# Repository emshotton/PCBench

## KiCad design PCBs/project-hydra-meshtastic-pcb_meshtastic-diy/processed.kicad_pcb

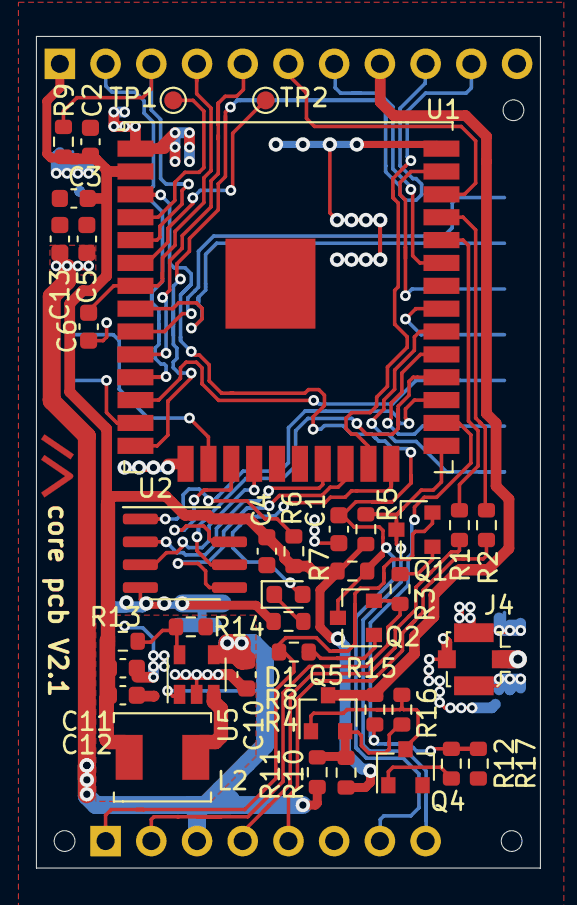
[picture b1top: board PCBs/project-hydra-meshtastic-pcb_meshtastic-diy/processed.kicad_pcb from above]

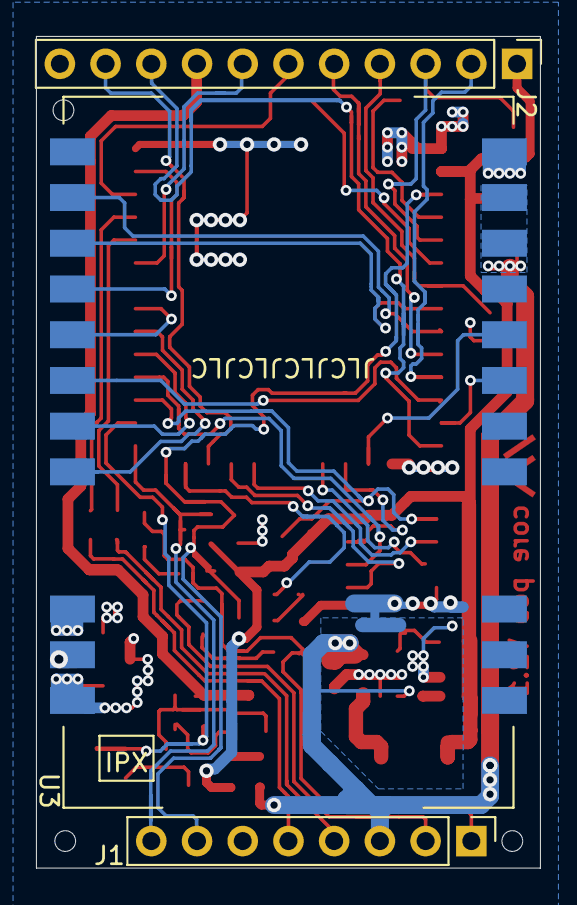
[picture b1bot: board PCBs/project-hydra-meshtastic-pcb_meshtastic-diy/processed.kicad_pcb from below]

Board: 2 copper layers, 28.0 x 46.2 mm, 47 parts (4 on the bottom side), 49 nets.

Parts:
C1, C2, C4, C5, C6: 100n; C_0603_1608Metric
C3, C10, C11, C12, C13: 22uF; C_0603_1608Metric
D1: LED; LED_0603_1608Metric
H1, H2, H3: tooling_hole; jlc_toolinghole
J1: programming header; PinHeader_1x08_P2.54mm_Vertical
J2: oled/gps/external HW; PinHeader_1x11_P2.54mm_Vertical
J4: ipex antenna; U.FL_Molex_MCRF_73412-0110_horizontal
L2: 4.7uH; chilsin_BMRA00040412
NT1: Net-Tie_2; NetTie-2_SMD_Pad0.5mm
Q1, Q2, Q4: BC848; SOT-23
Q5: CJ2301; SOT-23
R1, R8: 470; R_0603_1608Metric
R2, R10, R11, R16: 0; R_0603_1608Metric
R3, R4, R5, R6, R7, R9, R12, R15, R17: 10k; R_0603_1608Metric
R13: 536k; R_0603_1608Metric
R14: 118k; R_0603_1608Metric
SYM1: Meshtastic Logo; meshtastic_logo
TP1, TP2: TestPoint; TestPoint_Pad_D1.0mm
U1: ESP32-WROOM-32U
U2: ESP-PSRAM64; SOIC-8_3.9x4.9mm_P1.27mm
U3: E22-900M30S; e22-900m30s-handsoldering
U5: PAM2312; SOT-23-5

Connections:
+3V3: C2.1, C3.1, C4.1, C11.1, C12.1, J2.1, L2.2, R5.2, R6.2, R7.1, R9.2, R10.2, R13.1, U1.2, U2.8
+5V: C5.1, C10.1, C13.1, J1.3, R11.2, U3.9, U3.10, U5.1, U5.4
/5V_pwrctrl: J2.5, U1.10
/DTR: J1.1, Q1.2, R4.1
/EN: C1.1, J1.7, Q2.3, R7.2, U1.3
/ESP32_RX: R1.1, U1.34
/ESP32_TX: R2.1, U1.35
/GPIO0: J1.8, Q1.3, R5.1, U1.25
/GPIO2: D1.2, U1.24
/GPIO16: R6.1, U1.27, U2.1
/GPS_PWR_enable: R12.1, R16.2, R17.2, U1.26
/GPS_RX: J2.9, U1.14
/GPS_TX: J2.10, U1.23
/GPS_pwr: J2.8, Q5.3, R16.1
/RTS: J1.2, Q2.2, R3.1
/SCL: J2.6, U1.36
/SDA: J2.7, U1.33
/SDI_SD1: U1.22, U2.5
/SDO_SD0: U1.21, U2.2
/SHD_SD2: U1.17, U2.7
/SRAM_CLK: U1.28, U2.6
/SWP_SD3: U1.18, U2.3
/USR_BTN: J2.3, R9.1, U1.5
/e22_BUSY: U1.8, U3.14
/e22_DIO1: U1.9, U3.13
/e22_MISO: U1.31, U3.16
/e22_MOSI: U1.12, U3.17
/e22_NRST: U1.37, U3.15
/e22_NSS: U1.30, U3.19
/e22_RXEN: U1.13, U3.6
/e22_SCK: U1.29, U3.18
/e22_TXEN: U1.16, U3.7
/gpio_26: J2.2, U1.11
/vbat_mon: C6.1, J2.4, U1.7
GND: C1.2, C2.2, C3.2, C4.2, C5.2, C6.2, C13.2, J1.6, J2.11, J4.2, NT1.2, Q4.2, R8.2, R17.1, U1.1, U1.15, U1.38, U1.39, U2.4, U3.1, U3.2, U3.3, U3.4, U3.5, U3.11, U3.12, U3.20, U3.22
GNDA: C10.2, C11.2, C12.2, NT1.1, R14.2, U5.2
unnamed: D1.1, R8.1
unnamed: J1.4, R1.2
unnamed: J1.5, R2.2
unnamed: J4.1, U3.21
unnamed: L2.1, U5.3
unnamed: Q1.1, R3.2
unnamed: Q2.1, R4.2
unnamed: Q4.1, R12.2
unnamed: Q4.3, Q5.1, R15.1
unnamed: Q5.2, R10.1, R11.1, R15.2
unnamed: R13.2, R14.1, U5.5
unnamed: TP1.1, U1.4
unnamed: TP2.1, U1.6

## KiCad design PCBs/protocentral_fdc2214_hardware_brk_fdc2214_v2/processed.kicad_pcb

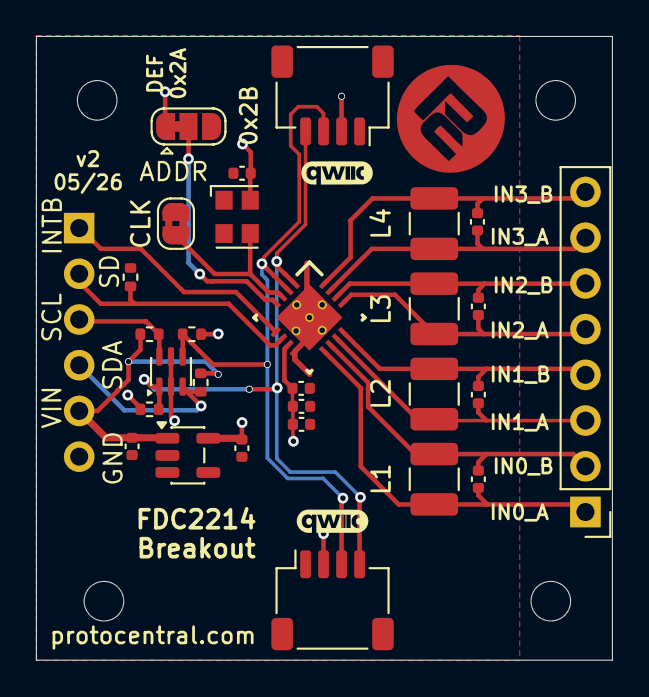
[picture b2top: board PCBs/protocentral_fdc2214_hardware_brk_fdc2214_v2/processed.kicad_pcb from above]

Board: 2 copper layers, 32.0 x 34.7 mm, 33 parts (0 on the bottom side), 19 nets.

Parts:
C1, C8: 1u; C_0402_1005Metric
C2: 2.2u; C_0402_1005Metric
C3, C9: 100n; C_0402_1005Metric
C4, C5, C6, C7: 33p; C_0402_1005Metric
C10: 10n; C_0402_1005Metric
CLK: SolderJumper_2_Bridged; SolderJumper-2_P1.3mm_Bridged2Bar_RoundedPad1.0x1.5mm
H1, H2, H3, H4: MountingHole; MountingHole_2.2mm_M2
J1: Conn_01x06; PinHeader_1x06_P2.54mm_Vertical
J2: Conn_01x08; PinHeader_1x08_P2.54mm_Vertical
J3, J4: Qwiic_RA; JST_SH_SM04B-SRSS-TB_1x04-1MP_P1.00mm_Horizontal
JP1: ADDR; SolderJumper-3_P1.3mm_Bridged12_RoundedPad1.0x1.5mm
L1, L2, L3, L4: 18uH, CMH322522-180KL; L_1210_3225Metric
R5, R8, R9, R12, R13: 10K; R_0402_1005Metric
U2: FDC2214RGHR; RGH0016A
U3: AP2112K-3.3; SOT-23-5
U4: BSS138DW-7-F; SOT-363_SC-70-6
Y1: KC2520Z; Oscillator_SMD_Kyocera_KC2520Z-4Pin_2.5x2.0mm

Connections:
+3V3: C2.1, C3.1, C8.1, C9.1, C10.1, J3.2, J4.2, JP1.1 (A), R8.1, R12.1, U2.7 (VDD), U3.5 (VOUT), U4.2 (G1), U4.5 (G2), Y1.4 (VCC)
GND: C1.2, C2.2, C3.2, C8.2, C9.2, C10.2, CLK.1 (A), J1.6, J3.1, J4.1, JP1.3 (B), R5.2, U2.8 (GND), U2.17, U3.2 (GND), Y1.2 (GND)
IN0_A: C4.1, J2.1, L1.2, U2.9 (IN0A)
IN0_B: C4.2, J2.2, L1.1, U2.10 (IN0B)
IN1_A: C5.1, J2.3, L2.2, U2.11 (IN1A)
IN1_B: C5.2, J2.4, L2.1, U2.12 (IN1B)
IN2_A: C6.1, J2.5, L3.2, U2.13 (IN2A)
IN2_B: C6.2, J2.6, L3.1, U2.14 (IN2B)
IN3_A: C7.1, J2.7, L4.2, U2.15 (IN3A)
IN3_B: C7.2, J2.8, L4.1, U2.16 (IN3B)
INTB: J1.1, U2.5 (INTB)
unnamed: JP1.2 (C), U2.4 (ADDR)
unnamed: CLK.2 (B), U2.3 (CLKIN), Y1.3 (CLK)
SCL: J1.3, R9.2, U4.6 (D1)
SCL_3V3: J3.4, J4.4, R8.2, U2.1 (SCL), U4.1 (S1)
SD: J1.2, R5.1, U2.6 (SD)
SDA: J1.4, R13.2, U4.3 (D2)
SDA_3V3: J3.3, J4.3, R12.2, U2.2 (SDA), U4.4 (S2)
VIN: C1.1, J1.5, R9.1, R13.1, U3.1 (VIN)

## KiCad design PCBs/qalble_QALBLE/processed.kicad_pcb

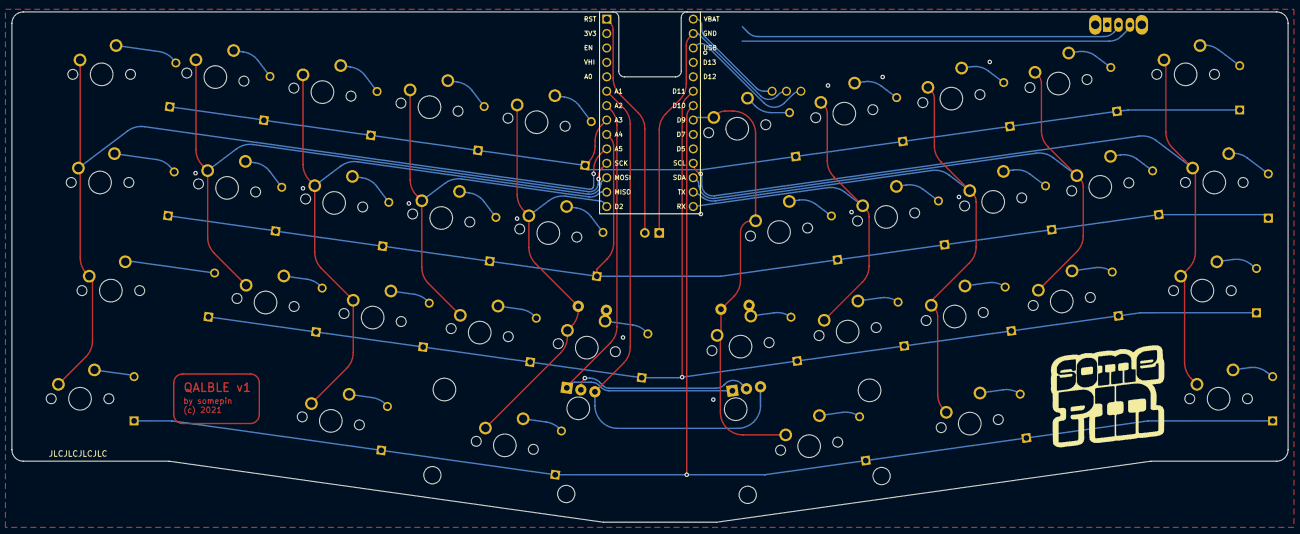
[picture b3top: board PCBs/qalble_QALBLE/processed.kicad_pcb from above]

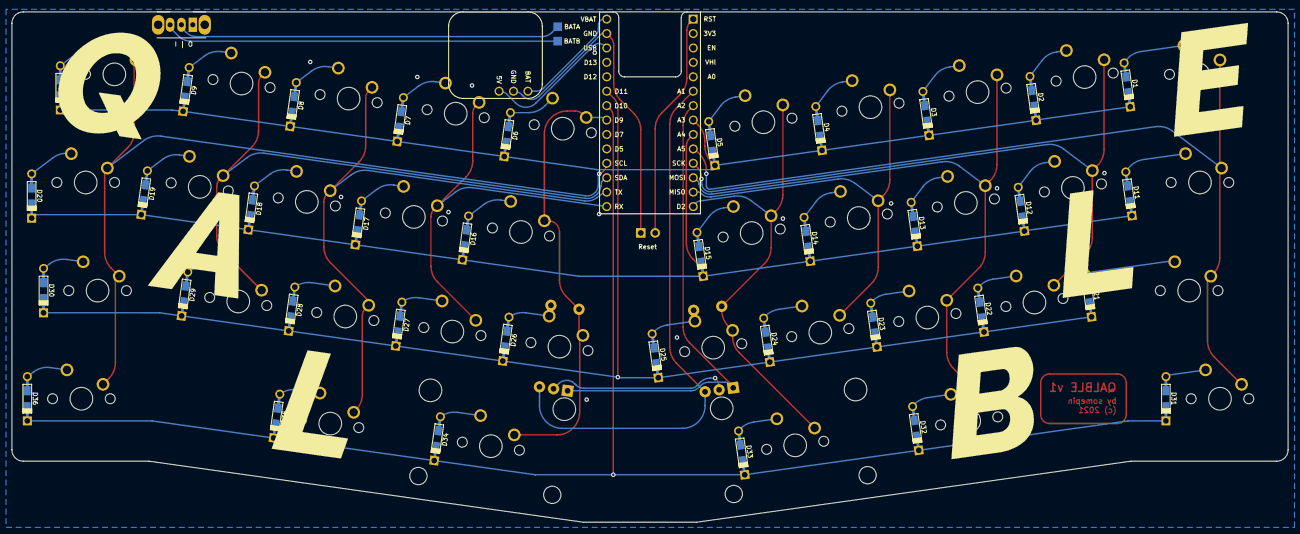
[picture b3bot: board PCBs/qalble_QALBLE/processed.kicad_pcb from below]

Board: 2 copper layers, 224.8 x 89.9 mm, 79 parts (3 on the bottom side), 58 nets.

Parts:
D1, D2, D3, D4, D5, D6, D7, D8, D9, D10, D11, D12, D13, D14, D15, D16, D17, D18, D19, D20, D21, D22, D23, D24, D25, D26, D27, D28, D29, D30, D31, D32, D33, D34, D35, D36: D_Small; Diode-Hybrid-Back
EN1, EN2: RotaryEncoder_Switch; RotaryEncoder_EC11
J1: Conn_01x02_Female; PinHeader_1x02_P2.54mm_Vertical
J2: Conn_01x02; Backpack Battery Jumper
MX1, MX2, MX3, MX4, MX5, MX6, MX7, MX8, MX9, MX12, MX13, MX14, MX15, MX16, MX17, MX18, MX19, MX20, MX22, MX23, MX24, MX25, MX26, MX27, MX28, MX29, MX31, MX32, MX35, MX36: MX-NoLED; MXOnly-1U-NoLED
MX10, MX11: MX-NoLED; MXOnly-1.25U-NoLED
MX21: MX-NoLED; MXOnly-1.75U-NoLED
MX30: MX-NoLED; MXOnly-1.5U-NoLED
MX33: MX-NoLED; MXOnly-2.25U-ReversedStabilizers-NoLED
MX34: MX-NoLED; MXOnly-2U-ReversedStabilizers-NoLED
SW1: SW_SPDT; SW_CuK_OS102011MA1QN1_SPDT_Angled
U1: Adafruit_ItsyBitsy_nRF52840; ItsyBitsy nRF52840
U2: Adafruit_Lipo_Backpack; Trinket Lipo Backpack

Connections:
BAT: U1.28 (VBAT), U2.3 (BAT)
BATA: J2.1, SW1.2 (B)
BATB: J2.2, SW1.3 (C)
COL0: MX1.1 (COL), MX11.1 (COL), MX21.1 (COL), MX31.1 (COL), U1.10 (A5)
COL1: MX2.1 (COL), MX12.1 (COL), MX22.1 (COL), U1.11 (SCK)
COL2: MX3.1 (COL), MX13.1 (COL), MX23.1 (COL), MX32.1 (COL), U1.12 (MOSI)
COL3: MX4.1 (COL), MX14.1 (COL), MX24.1 (COL), U1.13 (MISO)
COL4: EN1.S2, MX5.1 (COL), MX15.1 (COL), MX25.1 (COL), MX33.1 (COL), U1.14 (D2)
COL5: EN2.S2, MX6.1 (COL), MX16.1 (COL), MX26.1 (COL), MX34.1 (COL), U1.21 (D9)
COL6: MX7.1 (COL), MX17.1 (COL), MX27.1 (COL), U1.15 (RX)
COL7: MX8.1 (COL), MX18.1 (COL), MX28.1 (COL), MX35.1 (COL), U1.16 (TX)
COL8: MX9.1 (COL), MX19.1 (COL), MX29.1 (COL), U1.17 (SDA)
COL9: MX10.1 (COL), MX20.1 (COL), MX30.1 (COL), MX36.1 (COL), U1.18 (SCL)
ENCA: EN1.A, EN2.A, U1.7 (A2)
ENCB: EN1.B, EN2.B, U1.6 (A1)
GND: EN1.C, EN2.C, J1.1, U1.27 (GND), U2.2 (GND)
unnamed: D1.2 (A), MX1.2 (ROW)
unnamed: D2.2 (A), MX2.2 (ROW)
unnamed: D3.2 (A), MX3.2 (ROW)
unnamed: D4.2 (A), MX4.2 (ROW)
unnamed: D5.2 (A), MX5.2 (ROW)
unnamed: D6.2 (A), MX6.2 (ROW)
unnamed: D7.2 (A), MX7.2 (ROW)
unnamed: D8.2 (A), MX8.2 (ROW)
unnamed: D9.2 (A), MX9.2 (ROW)
unnamed: D10.2 (A), MX10.2 (ROW)
unnamed: D11.2 (A), MX11.2 (ROW)
unnamed: D12.2 (A), MX12.2 (ROW)
unnamed: D13.2 (A), MX13.2 (ROW)
unnamed: D14.2 (A), MX14.2 (ROW)
unnamed: D15.2 (A), MX15.2 (ROW)
unnamed: D16.2 (A), MX16.2 (ROW)
unnamed: D17.2 (A), MX17.2 (ROW)
unnamed: D18.2 (A), MX18.2 (ROW)
unnamed: D19.2 (A), MX19.2 (ROW)
unnamed: D20.2 (A), MX20.2 (ROW)
unnamed: D21.2 (A), MX21.2 (ROW)
unnamed: D22.2 (A), MX22.2 (ROW)
unnamed: D23.2 (A), MX23.2 (ROW)
unnamed: D24.2 (A), MX24.2 (ROW)
unnamed: D25.2 (A), EN1.S1, MX25.2 (ROW)
unnamed: D26.2 (A), EN2.S1, MX26.2 (ROW)
unnamed: D27.2 (A), MX27.2 (ROW)
unnamed: D28.2 (A), MX28.2 (ROW)
unnamed: D29.2 (A), MX29.2 (ROW)
unnamed: D30.2 (A), MX30.2 (ROW)
unnamed: D31.2 (A), MX31.2 (ROW)
unnamed: D32.2 (A), MX32.2 (ROW)
unnamed: D33.2 (A), MX33.2 (ROW)
unnamed: D34.2 (A), MX34.2 (ROW)
unnamed: D35.2 (A), MX35.2 (ROW)
unnamed: D36.2 (A), MX36.2 (ROW)
ROW0: D1.1 (K), D2.1 (K), D3.1 (K), D4.1 (K), D5.1 (K), D6.1 (K), D7.1 (K), D8.1 (K), D9.1 (K), D10.1 (K), U1.8 (A3)
ROW1: D11.1 (K), D12.1 (K), D13.1 (K), D14.1 (K), D15.1 (K), D16.1 (K), D17.1 (K), D18.1 (K), D19.1 (K), D20.1 (K), U1.9 (A4)
ROW2: D21.1 (K), D22.1 (K), D23.1 (K), D24.1 (K), D25.1 (K), D26.1 (K), D27.1 (K), D28.1 (K), D29.1 (K), D30.1 (K), U1.23 (D11)
ROW3: D31.1 (K), D32.1 (K), D33.1 (K), D34.1 (K), D35.1 (K), D36.1 (K), U1.22 (D10)
RST: J1.2, U1.1 (RST)
USB: U1.26 (USB), U2.1 (5V)

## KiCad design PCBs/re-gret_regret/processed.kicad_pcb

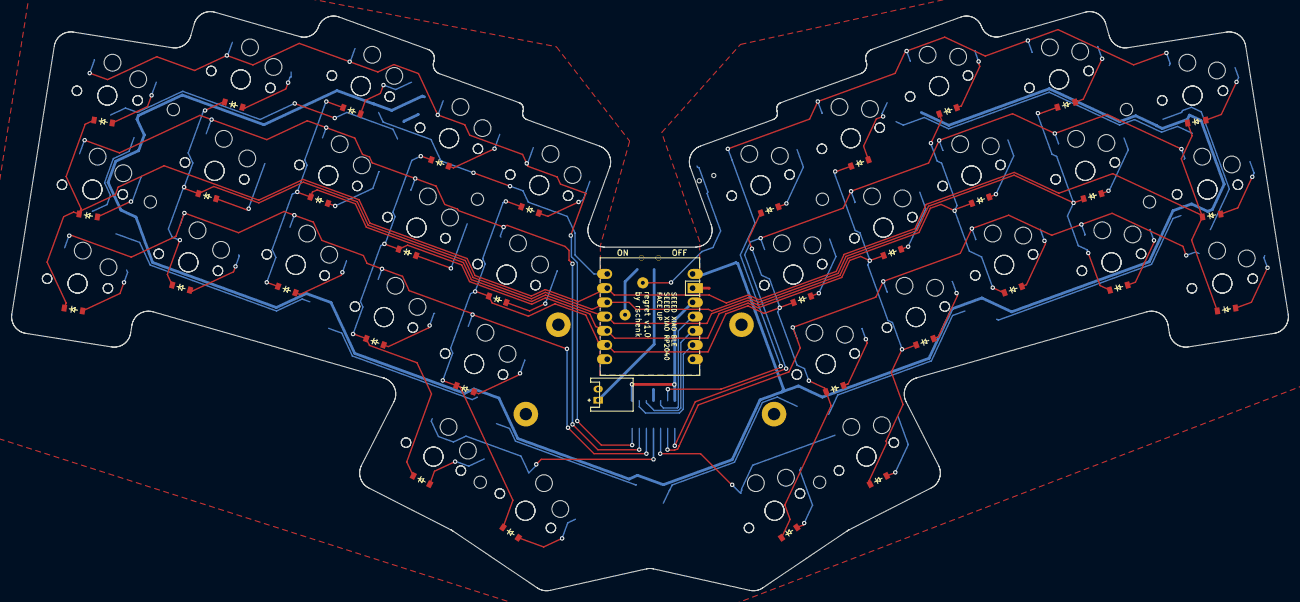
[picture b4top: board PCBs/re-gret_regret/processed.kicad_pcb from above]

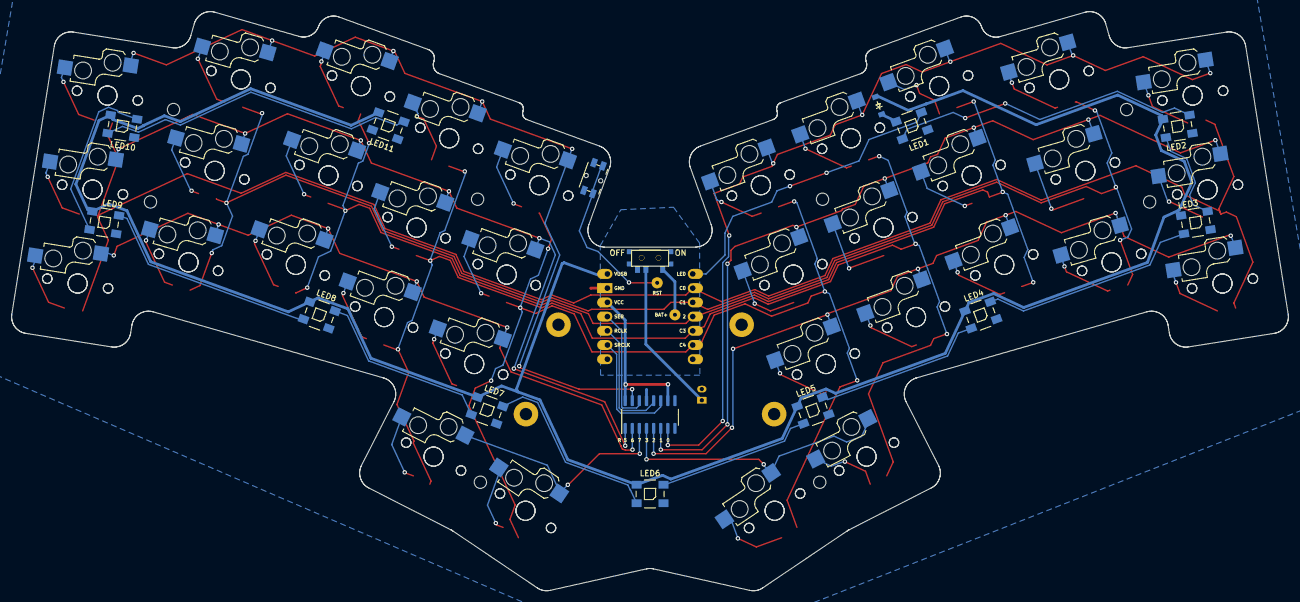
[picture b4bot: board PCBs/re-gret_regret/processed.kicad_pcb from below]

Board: 2 copper layers, 228.1 x 103.5 mm, 131 parts (13 on the bottom side), 68 nets.

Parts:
19.051: 74HC595; SOIC-16_3.9x9.9mm_P1.27mm
B1: Panasonic_EVQPUL_EVQPUC
D1, D2, D3, D4, D5, D6, D7, D8, D9, D10, D11, D12, D13, D14, D15, D16, D17, D18, D19, D20, D21, D22, D23, D24, D25, D26, D27, D28, D29, D30, D31, D32, D33, D34, D35: ComboDiode
JST1: JST_PH_S2B-PH-K_02x2.00mm_Angled
LED1, LED2, LED3, LED4, LED5, LED6, LED7, LED8, LED9, LED10, LED11: VAL**; WS2812B
MCU1: xiao-ble
PAD1, PAD2, PAD3, PAD4: MountingHole_2.2mm_M2_Pad
PAD5, PAD6, PAD7, PAD8, PAD9, PAD10, PAD11, PAD12: MountingHole_2.2mm_M2
S1, S2, S3, S4, S5, S6, S7, S8, S9, S10, S11, S12, S13, S14, S15, S16, S17, S18, S19, S20, S21, S22, S23, S24, S25, S26, S27, S28, S29, S30, S31, S32, S33, S34: PG1350
SB1, SB2, SB3, SB4, SB5, SB6, SB7, SB8, SB9, SB10, SB11, SB12, SB13, SB14, SB15, SB16, SB17, SB18, SB19, SB20, SB21, SB22, SB23, SB24, SB25, SB26, SB27, SB28, SB29, SB30, SB31, SB32, SB33, SB34: ChocBonusGoodies
T1: SPDT_C128955

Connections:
BAT+: MCU1.19, T1.1
BAT_POS: JST1.1, T1.2
C0: D1.1, D2.1, D3.1, D16.1, D17.1, D18.1, MCU1.2
C1: D4.1, D5.1, D6.1, D19.1, D20.1, D21.1, MCU1.3
C2: D7.1, D8.1, D9.1, D22.1, D23.1, D24.1, MCU1.4
C3: D10.1, D11.1, D12.1, D25.1, D26.1, D27.1, D31.1, D33.1, MCU1.5
C4: D13.1, D14.1, D15.1, D28.1, D29.1, D30.1, D32.1, D34.1, MCU1.6
GND: 19.051.8, 19.051.13, B1.2, JST1.2, LED1.3, LED2.3, LED3.3, LED4.3, LED5.3, LED6.3, LED7.3, LED8.3, LED9.3, LED10.3, LED11.3, MCU1.13
L2: LED1.2, LED2.4
L3: LED2.2, LED3.4
L4: LED3.2, LED4.4
L5: LED4.2, LED5.4
L6: LED5.2, LED6.4
L7: LED6.2, LED7.4
L8: LED7.2, LED8.4
L9: LED8.2, LED9.4
L10: LED9.2, LED10.4
L11: LED10.2, LED11.4
LED: LED1.4, MCU1.1
R0: 19.051.7, S3.1, S6.1, S9.1, S12.1, S15.1
R1: 19.051.6, S2.1, S5.1, S8.1, S11.1, S14.1
R2: 19.051.5, S1.1, S4.1, S7.1, S10.1, S13.1
R3: 19.051.4, S31.1, S32.1
R4: 19.051.15, S18.1, S21.1, S24.1, S27.1, S30.1
R5: 19.051.1, S17.1, S20.1, S23.1, S26.1, S29.1
R6: 19.051.2, S16.1, S19.1, S22.1, S25.1, S28.1
R7: 19.051.3, S33.1, S34.1
RCLK: 19.051.12, MCU1.10
RST: B1.1, MCU1.17
SER: 19.051.14, MCU1.11
SRCLK: 19.051.11, MCU1.9
VCC: 19.051.10, 19.051.16, MCU1.12
VUSB: D35.2, LED2.1, LED3.1, LED4.1, LED5.1, LED6.1, LED7.1, LED8.1, LED9.1, LED10.1, LED11.1, MCU1.14
home_thumb: D31.2, S31.2
index_bottom: D10.2, S10.2
index_home: D11.2, S11.2
index_top: D12.2, S12.2
inner_bottom: D13.2, S13.2
inner_home: D14.2, S14.2
inner_top: D15.2, S15.2
led_1_v: D35.1, LED1.1
middle_bottom: D7.2, S7.2
middle_home: D8.2, S8.2
middle_top: D9.2, S9.2
mirror_home_thumb: D33.2, S33.2
mirror_index_bottom: D25.2, S25.2
mirror_index_home: D26.2, S26.2
mirror_index_top: D27.2, S27.2
mirror_inner_bottom: D28.2, S28.2
mirror_inner_home: D29.2, S29.2
mirror_inner_top: D30.2, S30.2
mirror_middle_bottom: D22.2, S22.2
mirror_middle_home: D23.2, S23.2
mirror_middle_top: D24.2, S24.2
mirror_pinky_bottom: D16.2, S16.2
mirror_pinky_home: D17.2, S17.2
mirror_pinky_top: D18.2, S18.2
mirror_reachy_thumb: D34.2, S34.2
mirror_ring_bottom: D19.2, S19.2
mirror_ring_home: D20.2, S20.2
mirror_ring_top: D21.2, S21.2
pinky_bottom: D1.2, S1.2
pinky_home: D2.2, S2.2
pinky_top: D3.2, S3.2
reachy_thumb: D32.2, S32.2
ring_bottom: D4.2, S4.2
ring_home: D5.2, S5.2
ring_top: D6.2, S6.2

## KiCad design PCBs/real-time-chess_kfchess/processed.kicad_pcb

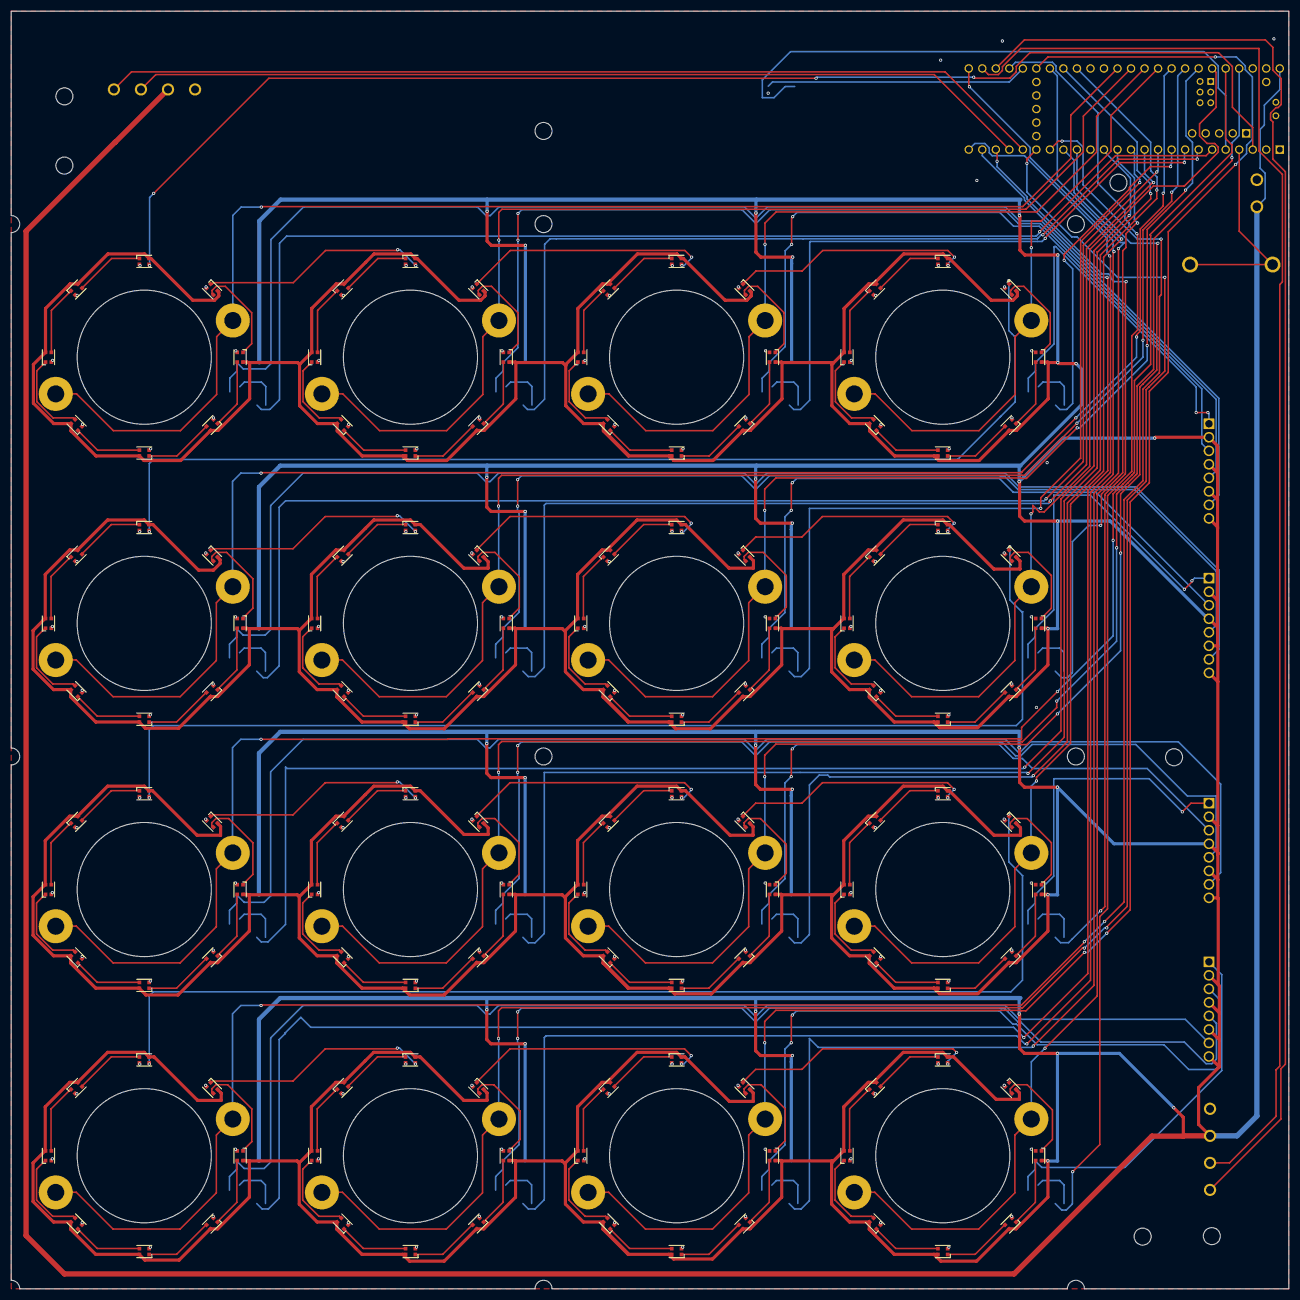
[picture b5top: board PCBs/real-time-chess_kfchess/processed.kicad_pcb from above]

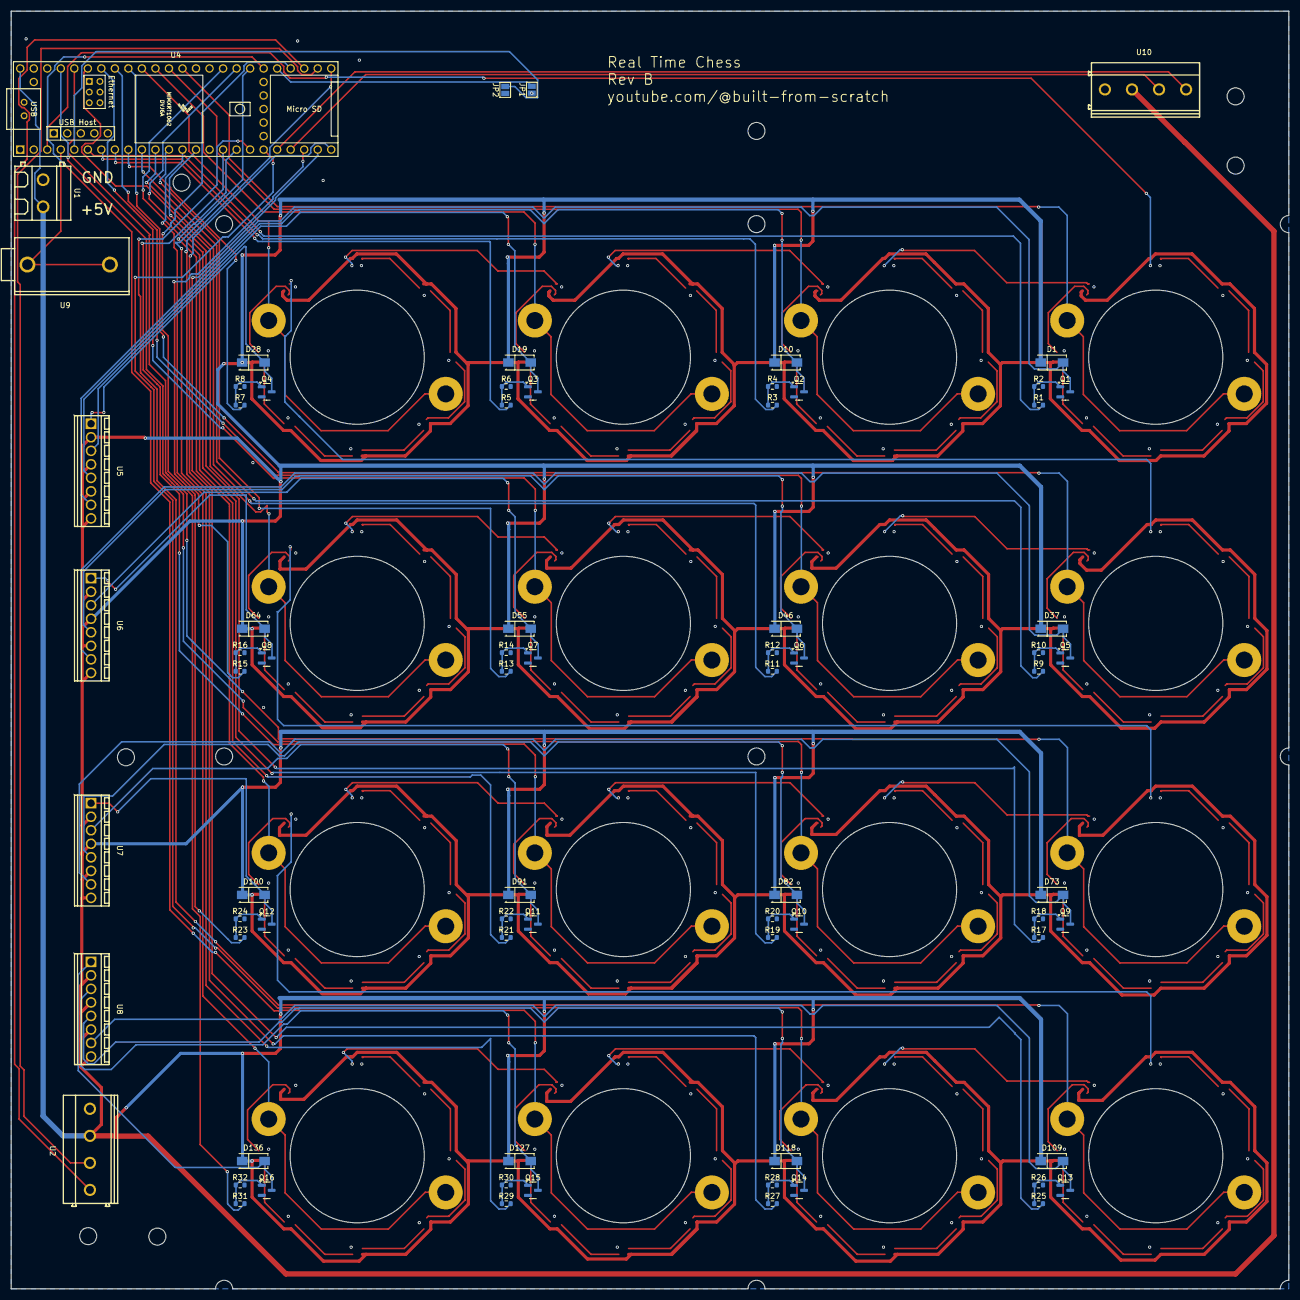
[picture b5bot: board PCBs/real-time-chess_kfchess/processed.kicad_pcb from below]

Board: 2 copper layers, 240.0 x 240.0 mm, 235 parts (75 on the bottom side), 201 nets.

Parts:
D1, D10, D19, D28, D37, D46, D55, D64, D73, D82, D91, D100, D109, D118, D127, D136: 1N4007_C727081; SMA_L4.3-W2.5-LS5.0-RD
D2, D3, D4, D5, D6, D7, D8, D9, D11, D12, D13, D14, D15, D16, D17, D18, D20, D21, D22, D23, D24, D25, D26, D27, D29, D30, D31, D32, D33, D34, D35, D36, D38, D39, D40, D41, D42, D43, D44, D45, D47, D48, D49, D50, D51, D52, D53, D54, D56, D57, D58, D59, D60, D61, D62, D63, D65, D66, D67, D68, D69, D70, D71, D72, D74, D75, D76, D77, D78, D79, D80, D81, D83, D84, D85, D86, D87, D88, D89, D90, D92, D93, D94, D95, D96, D97, D98, D99, D101, D102, D103, D104, D105, D106, D107, D108, D110, D111, D112, D113, D114, D115, D116, D117, D119, D120, D121, D122, D123, D124, D125, D126, D128, D129, D130, D131, D132, D133, D134, D135, D137, D138, D139, D140, D141, D142, D143, D144: WS2812B-2020; LED_WS2812B-2020_PLCC4_2.0x2.0mm
H1, H2, H3, H4, H5, H6, H7, H8, H9, H10, H11, H12, H13, H14, H15, H16, H17, H18, H19, H20, H21, H22, H23, H24, H25, H26, H27, H28, H29, H30, H31, H32: MountingHole_Pad; MountingHole_3.2mm_M3_Pad
JP1, JP2: SolderJumper_2_Open; SolderJumper-2_P1.3mm_Open_Pad1.0x1.5mm
Q1, Q2, Q3, Q4, Q5, Q6, Q7, Q8, Q9, Q10, Q11, Q12, Q13, Q14, Q15, Q16: AO3400A; SOT-23
R1, R3, R5, R7, R9, R11, R13, R15, R17, R19, R21, R23, R25, R27, R29, R31: 220; R_0603_1608Metric
R2, R4, R6, R8, R10, R12, R14, R16, R18, R20, R22, R24, R26, R28, R30, R32: 10k; R_0603_1608Metric
U1: KF128-5_08-2P; CONN-TH_P5.08_KF128-5.08-2P
U2, U10: DB128V-5_08-4P-GN-S; CONN-TH_4P-P5.08_DIBO_DB128V-5.08
U4: Teensy4.1; Teensy41
U5, U6, U7, U8: XY308-2_54-8P; CONN-TH_XY308-2.54-8P
U9: 24_243_2; CONN-TH_24.243.2

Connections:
+5V: D1.1 (K), D2.4 (VDD), D3.4 (VDD), D4.4 (VDD), D5.4 (VDD), D6.4 (VDD), D7.4 (VDD), D8.4 (VDD), D9.4 (VDD), D10.1 (K), D11.4 (VDD), D12.4 (VDD), D13.4 (VDD), D14.4 (VDD), D15.4 (VDD), D16.4 (VDD), D17.4 (VDD), D18.4 (VDD), D19.1 (K), D20.4 (VDD), D21.4 (VDD), D22.4 (VDD), D23.4 (VDD), D24.4 (VDD), D25.4 (VDD), D26.4 (VDD), D27.4 (VDD), D28.1 (K), D29.4 (VDD), D30.4 (VDD), D31.4 (VDD), D32.4 (VDD), D33.4 (VDD), D34.4 (VDD), D35.4 (VDD), D36.4 (VDD), D37.1 (K), D38.4 (VDD), D39.4 (VDD), D40.4 (VDD), D41.4 (VDD), D42.4 (VDD), D43.4 (VDD), D44.4 (VDD), D45.4 (VDD), D46.1 (K), D47.4 (VDD), D48.4 (VDD), D49.4 (VDD), D50.4 (VDD), D51.4 (VDD), D52.4 (VDD), D53.4 (VDD), D54.4 (VDD), D55.1 (K), D56.4 (VDD), D57.4 (VDD), D58.4 (VDD), D59.4 (VDD), D60.4 (VDD), D61.4 (VDD), D62.4 (VDD), D63.4 (VDD), D64.1 (K), D65.4 (VDD), D66.4 (VDD), D67.4 (VDD), D68.4 (VDD), D69.4 (VDD), D70.4 (VDD), D71.4 (VDD), D72.4 (VDD), D73.1 (K), D74.4 (VDD), D75.4 (VDD), D76.4 (VDD), D77.4 (VDD), D78.4 (VDD), D79.4 (VDD), D80.4 (VDD), D81.4 (VDD), D82.1 (K), D83.4 (VDD), D84.4 (VDD), D85.4 (VDD), D86.4 (VDD), D87.4 (VDD), D88.4 (VDD), D89.4 (VDD), D90.4 (VDD), D91.1 (K), D92.4 (VDD), D93.4 (VDD), D94.4 (VDD), D95.4 (VDD), D96.4 (VDD), D97.4 (VDD), D98.4 (VDD), D99.4 (VDD), D100.1 (K), D101.4 (VDD), D102.4 (VDD), D103.4 (VDD), D104.4 (VDD), D105.4 (VDD), D106.4 (VDD), D107.4 (VDD), D108.4 (VDD), D109.1 (K), D110.4 (VDD), D111.4 (VDD), D112.4 (VDD), D113.4 (VDD), D114.4 (VDD), D115.4 (VDD), D116.4 (VDD), D117.4 (VDD), D118.1 (K), D119.4 (VDD), D120.4 (VDD), D121.4 (VDD), D122.4 (VDD), D123.4 (VDD), D124.4 (VDD), D125.4 (VDD), D126.4 (VDD), D127.1 (K), D128.4 (VDD), D129.4 (VDD), D130.4 (VDD), D131.4 (VDD), D132.4 (VDD), D133.4 (VDD), D134.4 (VDD), D135.4 (VDD), D136.1 (K), D137.4 (VDD), D138.4 (VDD), D139.4 (VDD), D140.4 (VDD), D141.4 (VDD), D142.4 (VDD), D143.4 (VDD), D144.4 (VDD), U1.2, U2.3, U4.48 (VIN), U5.2, U5.4, U5.6, U5.8, U6.2, U6.4, U6.6, U6.8, U7.2, U7.4, U7.6, U7.8, U8.2, U8.4, U8.6, U8.8, U10.2
/c11: R1.2, U4.6 (4_BCLK2)
/c12: R3.2, U4.7 (5_IN2)
/c13: R5.2, U4.8 (6_OUT1D)
/c14: R7.2, U4.9 (7_RX2_OUT1A)
/c21: R9.2, U4.10 (8_TX2_IN1)
/c22: R11.2, U4.11 (9_OUT1C)
/c23: R13.2, U4.12 (10_CS_MQSR)
/c24: R15.2, U4.13 (11_MOSI_CTX1)
/c31: R17.2, U4.14 (12_MISO_MQSL)
/c32: R19.2, U4.32 (40_A16)
/c33: R21.2, U4.33 (41_A17)
/c34: R23.2, U4.22 (30_CRX3)
/c41: R25.2, U4.23 (31_CTX3)
/c42: R27.2, U4.24 (32_OUT1B)
/c43: R29.2, U4.25 (33_MCLK2)
/c44: R31.2, U4.28 (36_CS)
/jp1: JP1.2 (B), U4.29 (37_CS)
/jp2: JP2.2 (B), U4.5 (3_LRCLK2)
/leds: D2.3 (DIN), U4.3 (1_TX1_CTX2_MISO1)
/row1/d_out: D36.1 (DOUT), D38.3 (DIN)
/row1/square1/d_out: D9.1 (DOUT), D11.3 (DIN)
/row1/square1/em_n: D1.2 (A), Q1.3 (D), U5.7
/row1/square2/d_out: D18.1 (DOUT), D20.3 (DIN)
/row1/square2/em_n: D10.2 (A), Q2.3 (D), U5.5
/row1/square3/d_out: D27.1 (DOUT), D29.3 (DIN)
/row1/square3/em_n: D19.2 (A), Q3.3 (D), U5.3
/row1/square4/em_n: D28.2 (A), Q4.3 (D), U5.1
/row2/d_out: D72.1 (DOUT), D74.3 (DIN)
/row2/square1/d_out: D45.1 (DOUT), D47.3 (DIN)
/row2/square1/em_n: D37.2 (A), Q5.3 (D), U6.7
/row2/square2/d_out: D54.1 (DOUT), D56.3 (DIN)
/row2/square2/em_n: D46.2 (A), Q6.3 (D), U6.5
/row2/square3/d_out: D63.1 (DOUT), D65.3 (DIN)
/row2/square3/em_n: D55.2 (A), Q7.3 (D), U6.3
/row2/square4/em_n: D64.2 (A), Q8.3 (D), U6.1
/row3/d_out: D108.1 (DOUT), D110.3 (DIN)
/row3/square1/d_out: D81.1 (DOUT), D83.3 (DIN)
/row3/square1/em_n: D73.2 (A), Q9.3 (D), U7.7
/row3/square2/d_out: D90.1 (DOUT), D92.3 (DIN)
/row3/square2/em_n: D82.2 (A), Q10.3 (D), U7.5
/row3/square3/d_out: D99.1 (DOUT), D101.3 (DIN)
/row3/square3/em_n: D91.2 (A), Q11.3 (D), U7.3
/row3/square4/em_n: D100.2 (A), Q12.3 (D), U7.1
/row4/square1/d_out: D117.1 (DOUT), D119.3 (DIN)
/row4/square1/em_n: D109.2 (A), Q13.3 (D), U8.7
/row4/square2/d_out: D126.1 (DOUT), D128.3 (DIN)
/row4/square2/em_n: D118.2 (A), Q14.3 (D), U8.5
/row4/square3/d_out: D135.1 (DOUT), D137.3 (DIN)
/row4/square3/em_n: D127.2 (A), Q15.3 (D), U8.3
/row4/square4/em_n: D136.2 (A), Q16.3 (D), U8.1
/rx_in: U4.20 (28_RX7), U10.4
/rx_out: U2.2, U4.26 (34_RX8)
/s11: H1.1, H2.1, U4.36 (14_A0_TX3_SPDIF_OUT)
/s12: H3.1, H4.1, U4.37 (15_A1_RX3_SPDIF_IN)
/s13: H5.1, H6.1, U4.38 (16_A2_RX4_SCL1)
/s14: H7.1, H8.1, U4.39 (17_A3_TX4_SDA1)
/s21: H9.1, H10.1, U4.40 (18_A4_SDA)
/s22: H11.1, H12.1, U4.41 (19_A5_SCL)
/s23: H13.1, H14.1, U4.42 (20_A6_TX5_LRCLK1)
/s24: H15.1, H16.1, U4.43 (21_A7_RX5_BCLK1)
/s31: H17.1, H18.1, U4.44 (22_A8_CTX1)
/s32: H19.1, H20.1, U4.45 (23_A9_CRX1_MCLK1)
/s33: H21.1, H22.1, U4.16 (24_A10_TX6_SCL2)
/s34: H23.1, H24.1, U4.17 (25_A11_RX6_SDA2)
/s41: H25.1, H26.1, U4.18 (26_A12_MOSI1)
/s42: H27.1, H28.1, U4.19 (27_A13_SCK1)
/s43: H29.1, H30.1, U4.30 (38_CS1_IN1)
/s44: H31.1, H32.1, U4.31 (39_MISO1_OUT1A)
/tx_in: U4.21 (29_TX7), U10.3
/tx_out: U2.1, U4.27 (35_TX8)
GND: D2.2 (VSS), D3.2 (VSS), D4.2 (VSS), D5.2 (VSS), D6.2 (VSS), D7.2 (VSS), D8.2 (VSS), D9.2 (VSS), D11.2 (VSS), D12.2 (VSS), D13.2 (VSS), D14.2 (VSS), D15.2 (VSS), D16.2 (VSS), D17.2 (VSS), D18.2 (VSS), D20.2 (VSS), D21.2 (VSS), D22.2 (VSS), D23.2 (VSS), D24.2 (VSS), D25.2 (VSS), D26.2 (VSS), D27.2 (VSS), D29.2 (VSS), D30.2 (VSS), D31.2 (VSS), D32.2 (VSS), D33.2 (VSS), D34.2 (VSS), D35.2 (VSS), D36.2 (VSS), D38.2 (VSS), D39.2 (VSS), D40.2 (VSS), D41.2 (VSS), D42.2 (VSS), D43.2 (VSS), D44.2 (VSS), D45.2 (VSS), D47.2 (VSS), D48.2 (VSS), D49.2 (VSS), D50.2 (VSS), D51.2 (VSS), D52.2 (VSS), D53.2 (VSS), D54.2 (VSS), D56.2 (VSS), D57.2 (VSS), D58.2 (VSS), D59.2 (VSS), D60.2 (VSS), D61.2 (VSS), D62.2 (VSS), D63.2 (VSS), D65.2 (VSS), D66.2 (VSS), D67.2 (VSS), D68.2 (VSS), D69.2 (VSS), D70.2 (VSS), D71.2 (VSS), D72.2 (VSS), D74.2 (VSS), D75.2 (VSS), D76.2 (VSS), D77.2 (VSS), D78.2 (VSS), D79.2 (VSS), D80.2 (VSS), D81.2 (VSS), D83.2 (VSS), D84.2 (VSS), D85.2 (VSS), D86.2 (VSS), D87.2 (VSS), D88.2 (VSS), D89.2 (VSS), D90.2 (VSS), D92.2 (VSS), D93.2 (VSS), D94.2 (VSS), D95.2 (VSS), D96.2 (VSS), D97.2 (VSS), D98.2 (VSS), D99.2 (VSS), D101.2 (VSS), D102.2 (VSS), D103.2 (VSS), D104.2 (VSS), D105.2 (VSS), D106.2 (VSS), D107.2 (VSS), D108.2 (VSS), D110.2 (VSS), D111.2 (VSS), D112.2 (VSS), D113.2 (VSS), D114.2 (VSS), D115.2 (VSS), D116.2 (VSS), D117.2 (VSS), D119.2 (VSS), D120.2 (VSS), D121.2 (VSS), D122.2 (VSS), D123.2 (VSS), D124.2 (VSS), D125.2 (VSS), D126.2 (VSS), D128.2 (VSS), D129.2 (VSS), D130.2 (VSS), D131.2 (VSS), D132.2 (VSS), D133.2 (VSS), D134.2 (VSS), D135.2 (VSS), D137.2 (VSS), D138.2 (VSS), D139.2 (VSS), D140.2 (VSS), D141.2 (VSS), D142.2 (VSS), D143.2 (VSS), D144.2 (VSS), JP1.1 (A), JP2.1 (A), Q1.2 (S), Q2.2 (S), Q3.2 (S), Q4.2 (S), Q5.2 (S), Q6.2 (S), Q7.2 (S), Q8.2 (S), Q9.2 (S), Q10.2 (S), Q11.2 (S), Q12.2 (S), Q13.2 (S), Q14.2 (S), Q15.2 (S), Q16.2 (S), R2.2, R4.2, R6.2, R8.2, R10.2, R12.2, R14.2, R16.2, R18.2, R20.2, R22.2, R24.2, R26.2, R28.2, R30.2, R32.2, U1.1, U2.4, U4.1 (GND), U4.34 (GND), U4.47 (GND), U10.1
unnamed: D2.1 (DOUT), D3.3 (DIN)
unnamed: D3.1 (DOUT), D4.3 (DIN)
unnamed: D4.1 (DOUT), D5.3 (DIN)
unnamed: D5.1 (DOUT), D6.3 (DIN)
unnamed: D6.1 (DOUT), D7.3 (DIN)
unnamed: D7.1 (DOUT), D8.3 (DIN)
unnamed: D8.1 (DOUT), D9.3 (DIN)
unnamed: D11.1 (DOUT), D12.3 (DIN)
unnamed: D12.1 (DOUT), D13.3 (DIN)
unnamed: D13.1 (DOUT), D14.3 (DIN)
unnamed: D14.1 (DOUT), D15.3 (DIN)
unnamed: D15.1 (DOUT), D16.3 (DIN)
unnamed: D16.1 (DOUT), D17.3 (DIN)
unnamed: D17.1 (DOUT), D18.3 (DIN)
unnamed: D20.1 (DOUT), D21.3 (DIN)
unnamed: D21.1 (DOUT), D22.3 (DIN)
unnamed: D22.1 (DOUT), D23.3 (DIN)
unnamed: D23.1 (DOUT), D24.3 (DIN)
unnamed: D24.1 (DOUT), D25.3 (DIN)
unnamed: D25.1 (DOUT), D26.3 (DIN)
unnamed: D26.1 (DOUT), D27.3 (DIN)
unnamed: D29.1 (DOUT), D30.3 (DIN)
unnamed: D30.1 (DOUT), D31.3 (DIN)
unnamed: D31.1 (DOUT), D32.3 (DIN)
unnamed: D32.1 (DOUT), D33.3 (DIN)
unnamed: D33.1 (DOUT), D34.3 (DIN)
unnamed: D34.1 (DOUT), D35.3 (DIN)
unnamed: D35.1 (DOUT), D36.3 (DIN)
unnamed: D38.1 (DOUT), D39.3 (DIN)
unnamed: D39.1 (DOUT), D40.3 (DIN)
unnamed: D40.1 (DOUT), D41.3 (DIN)
unnamed: D41.1 (DOUT), D42.3 (DIN)
unnamed: D42.1 (DOUT), D43.3 (DIN)
unnamed: D43.1 (DOUT), D44.3 (DIN)
unnamed: D44.1 (DOUT), D45.3 (DIN)
unnamed: D47.1 (DOUT), D48.3 (DIN)
unnamed: D48.1 (DOUT), D49.3 (DIN)
unnamed: D49.1 (DOUT), D50.3 (DIN)
unnamed: D50.1 (DOUT), D51.3 (DIN)
unnamed: D51.1 (DOUT), D52.3 (DIN)
unnamed: D52.1 (DOUT), D53.3 (DIN)
unnamed: D53.1 (DOUT), D54.3 (DIN)
unnamed: D56.1 (DOUT), D57.3 (DIN)
unnamed: D57.1 (DOUT), D58.3 (DIN)
unnamed: D58.1 (DOUT), D59.3 (DIN)
unnamed: D59.1 (DOUT), D60.3 (DIN)
unnamed: D60.1 (DOUT), D61.3 (DIN)
unnamed: D61.1 (DOUT), D62.3 (DIN)
unnamed: D62.1 (DOUT), D63.3 (DIN)
unnamed: D65.1 (DOUT), D66.3 (DIN)
unnamed: D66.1 (DOUT), D67.3 (DIN)
unnamed: D67.1 (DOUT), D68.3 (DIN)
unnamed: D68.1 (DOUT), D69.3 (DIN)
unnamed: D69.1 (DOUT), D70.3 (DIN)
unnamed: D70.1 (DOUT), D71.3 (DIN)
unnamed: D71.1 (DOUT), D72.3 (DIN)
unnamed: D74.1 (DOUT), D75.3 (DIN)
unnamed: D75.1 (DOUT), D76.3 (DIN)
unnamed: D76.1 (DOUT), D77.3 (DIN)
unnamed: D77.1 (DOUT), D78.3 (DIN)
unnamed: D78.1 (DOUT), D79.3 (DIN)
unnamed: D79.1 (DOUT), D80.3 (DIN)
unnamed: D80.1 (DOUT), D81.3 (DIN)
unnamed: D83.1 (DOUT), D84.3 (DIN)
unnamed: D84.1 (DOUT), D85.3 (DIN)
unnamed: D85.1 (DOUT), D86.3 (DIN)
unnamed: D86.1 (DOUT), D87.3 (DIN)
unnamed: D87.1 (DOUT), D88.3 (DIN)
unnamed: D88.1 (DOUT), D89.3 (DIN)
unnamed: D89.1 (DOUT), D90.3 (DIN)
unnamed: D92.1 (DOUT), D93.3 (DIN)
unnamed: D93.1 (DOUT), D94.3 (DIN)
unnamed: D94.1 (DOUT), D95.3 (DIN)
unnamed: D95.1 (DOUT), D96.3 (DIN)
unnamed: D96.1 (DOUT), D97.3 (DIN)
unnamed: D97.1 (DOUT), D98.3 (DIN)
unnamed: D98.1 (DOUT), D99.3 (DIN)
unnamed: D101.1 (DOUT), D102.3 (DIN)
unnamed: D102.1 (DOUT), D103.3 (DIN)
unnamed: D103.1 (DOUT), D104.3 (DIN)
unnamed: D104.1 (DOUT), D105.3 (DIN)
unnamed: D105.1 (DOUT), D106.3 (DIN)
unnamed: D106.1 (DOUT), D107.3 (DIN)
unnamed: D107.1 (DOUT), D108.3 (DIN)
unnamed: D110.1 (DOUT), D111.3 (DIN)
unnamed: D111.1 (DOUT), D112.3 (DIN)
unnamed: D112.1 (DOUT), D113.3 (DIN)
unnamed: D113.1 (DOUT), D114.3 (DIN)
unnamed: D114.1 (DOUT), D115.3 (DIN)
unnamed: D115.1 (DOUT), D116.3 (DIN)
unnamed: D116.1 (DOUT), D117.3 (DIN)
unnamed: D119.1 (DOUT), D120.3 (DIN)
unnamed: D120.1 (DOUT), D121.3 (DIN)
unnamed: D121.1 (DOUT), D122.3 (DIN)
unnamed: D122.1 (DOUT), D123.3 (DIN)
unnamed: D123.1 (DOUT), D124.3 (DIN)
unnamed: D124.1 (DOUT), D125.3 (DIN)
unnamed: D125.1 (DOUT), D126.3 (DIN)
unnamed: D128.1 (DOUT), D129.3 (DIN)
unnamed: D129.1 (DOUT), D130.3 (DIN)
unnamed: D130.1 (DOUT), D131.3 (DIN)
unnamed: D131.1 (DOUT), D132.3 (DIN)
unnamed: D132.1 (DOUT), D133.3 (DIN)
unnamed: D133.1 (DOUT), D134.3 (DIN)
unnamed: D134.1 (DOUT), D135.3 (DIN)
unnamed: D137.1 (DOUT), D138.3 (DIN)
unnamed: D138.1 (DOUT), D139.3 (DIN)
unnamed: D139.1 (DOUT), D140.3 (DIN)
unnamed: D140.1 (DOUT), D141.3 (DIN)
unnamed: D141.1 (DOUT), D142.3 (DIN)
unnamed: D142.1 (DOUT), D143.3 (DIN)
unnamed: D143.1 (DOUT), D144.3 (DIN)
unnamed: Q1.1 (G), R1.1, R2.1
unnamed: Q2.1 (G), R3.1, R4.1
unnamed: Q3.1 (G), R5.1, R6.1
unnamed: Q4.1 (G), R7.1, R8.1
unnamed: Q5.1 (G), R9.1, R10.1
unnamed: Q6.1 (G), R11.1, R12.1
unnamed: Q7.1 (G), R13.1, R14.1
unnamed: Q8.1 (G), R15.1, R16.1
unnamed: Q9.1 (G), R17.1, R18.1
unnamed: Q10.1 (G), R19.1, R20.1
unnamed: Q11.1 (G), R21.1, R22.1
unnamed: Q12.1 (G), R23.1, R24.1
unnamed: Q13.1 (G), R25.1, R26.1
unnamed: Q14.1 (G), R27.1, R28.1
unnamed: Q15.1 (G), R29.1, R30.1
unnamed: Q16.1 (G), R31.1, R32.1
unnamed: U4.4 (2_OUT2), U9.1, U9.2

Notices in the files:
PCBs/qalble_QALBLE/processed.kicad_pcb:
(c) 2021
